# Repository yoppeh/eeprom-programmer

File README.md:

# eeprom-programmer
An Arduino Nano sketch and schematic for an Atmel 28cx programmer. The schematic started out only targeting 8kx8 chips (rev. A) but has been updated to connect all address lines for the 28cx series (rev. B), so any of those eeproms should work up to the 32kx8 chips. The design is based on [this one](https://youtu.be/K88pgWhEb1M), from Ben Eater. 

The Arduino Nano sketch implements a serial interface to the programmer. It accepts one-letter commands:
- e - erase the eeprom
- f - fill eeprom with incrementing bytes
- h - help (this) text
- l - lock the eeprom against writes
- r - read and dump eeprom contents
- s - set the size of the eeprom
- u - unlock eeprom writes
- v - software version info
- x - xmodem transfer binary file to eeprom

Any standard terminal program can be used to talk to the programmer. I use the following:
- [serial](http://www.decisivetactics.com/products/serial/) for the Mac
- [teraterm](https://ttssh2.osdn.jp/index.html.en) for Windows
- [minicom](https://linux.die.net/man/1/minicom) for Linux

Be sure to set the size of your target eeprom with the s command before doing anything. It doesn't affect the chip in any way, but tells the programmer what size your chip is for the erase, fill and read commands and error checking in the xmodem transfer.

The programmer uses standard x-modem, as provided by any respectable terminal program—and certainly all of the
above listed terminal programs—to put binary files onto the eeprom. No other software is required. The programmer
will verify every 64 bytes as they are written (the size of an internal eeprom page).

Although the eeprom chips are supposed to come from the factory unlocked, I've heard stories of some chips being
purchased off ebay that arrive locked. Try doing an unlock on a chip if you have problems writing to it.

When doing an xmodem transfer to the chip, the program will wait indefinitely for you to start the xmodem transfer from your terminal software. You can abort the transfer at this point by pressing the ESC key. Otherwise, once you have started the transfer, it will continue until the process completes or an error is detected.

If you want to fill the eeprom with a specific byte, say the 6502 nop 0xea, just change

    fill[j] = i + j; 
on line 490 to

    fill[j] = 0xea;

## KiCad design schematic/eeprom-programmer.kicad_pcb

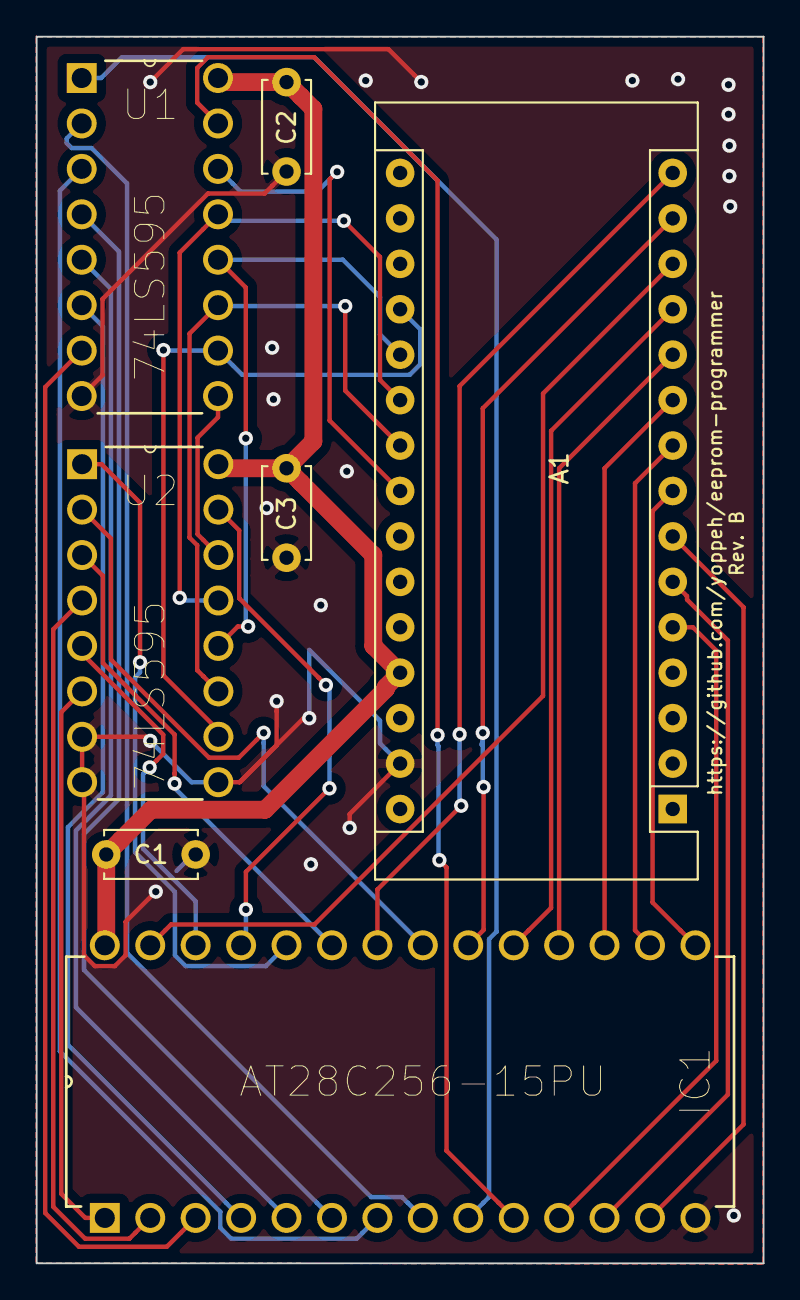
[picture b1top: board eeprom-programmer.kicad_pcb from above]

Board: 2 copper layers, 40.6 x 68.6 mm, 7 parts (0 on the bottom side), 34 nets.

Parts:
A1: Arduino_Nano_v3.x; Arduino_Nano
C1, C2, C3: .1uf; C_Disc_D5.0mm_W2.5mm_P5.00mm
IC1: AT28C256-15PU; DIP254P1524X482-28
U1, U2: 74LS595; DIP254P762X508-16

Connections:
/addr00: IC1.10, U1.15
/addr01: IC1.9, U1.1
/addr02: IC1.8, U1.2
/addr03: IC1.7, U1.3
/addr04: IC1.6, U1.4
/addr05: IC1.5, U1.5
/addr06: IC1.4, U1.6
/addr07: IC1.3, U1.7
/addr08: IC1.25, U2.15
/addr09: IC1.24, U2.1
/addr10: IC1.21, U2.2
/addr11: IC1.23, U2.3
/addr12: IC1.2, U2.4
/addr13: IC1.26, U2.5
/addr14: IC1.1, U2.6
/data0: A1.5, IC1.11
/data1: A1.6, IC1.12
/data2: A1.7, IC1.13
/data3: A1.8, IC1.15
/data4: A1.9, IC1.16
/data5: A1.10, IC1.17
/data6: A1.11, IC1.18
/data7: A1.12, IC1.19
Arduino5V: A1.27, C1.2, C2.2, C3.2, IC1.28, U1.16, U2.16
GND: A1.29, C1.1, C2.1, C3.1, IC1.14, U1.8, U2.7, U2.8, U2.9
unnamed: U1.9, U2.14
eeNotChipEnable: A1.14, IC1.20
eeNotOutputEnable: A1.15, IC1.22
eeNotWriteEnable: A1.13, IC1.27
srNotOutputEnable: A1.21, U1.13, U2.13
srNotResetAll: A1.19, U1.10, U2.10
srReadClock: A1.20, U1.12, U2.12
srSerialClock: A1.22, U1.11, U2.11
srSerialData: A1.23, U1.14

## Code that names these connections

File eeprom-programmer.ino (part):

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 *     PORTD, bit 3 = I/O1
 *     PORTD, bit 2 = I/O0
 */
const int srSerialData = A4;
const int srSerialClock = A3;
const int srNotOutputEnable = A2;
const int srReadClock = A1;
const int srNotResetAll = A0;
const int eeNotWriteEnable = 10;
const int eeNotChipEnable = 11;
const int eeNotOutputEnable = 12;
const int eeD0 = 2;
const int eeD1 = 3;
const int eeD2 = 4;
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 */
void setup() 
{
    pinMode(srSerialData, OUTPUT);
    pinMode(srSerialClock, OUTPUT);
    pinMode(srNotOutputEnable, OUTPUT);
    pinMode(srReadClock, OUTPUT);
    pinMode(srNotResetAll, OUTPUT);
    pinMode(eeNotWriteEnable, OUTPUT);
    pinMode(eeNotChipEnable, OUTPUT);
    pinMode(eeNotOutputEnable, OUTPUT);
  
    pinMode(LED_BUILTIN, OUTPUT);
    
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
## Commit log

2019-04-11 Tidy up the schematic a bit
2019-04-17 Rearrange the repo
2019-04-17 Add local library
2019-04-17 Rename files
2019-04-17 Readd Arduino and EEPROM symbols
2019-04-17 Remove excess wires
2019-04-17 Add busses
2019-04-17 Tighten up schematic
2019-04-18 Add PCB
2019-04-19 Initial PCB routing
2019-04-19 Fix issues for OSHPARK submission
2019-04-20 First prototype board
2019-04-21 Add verify to xmodem write
2019-04-23 Add evidence of existence
2019-04-23 Sync comments with code changes
2019-04-23 Auto-display help output on startup
2019-04-23 Add more text to README
2019-04-23 Fix whitespace
2019-04-24 Add picture of terminal window
2019-04-26 Use assets branch
2019-04-26 Fix image syntax for serial screenshot
2019-04-26 Show the screenshot without the text
2019-04-26 Remove images
2019-05-04 Port mappings changed for PCB
2019-05-04 Change revision to 'a'
2019-05-06 Update for schematic changes
2019-05-06 Remove pointless shift
2019-05-07 Remove executable permissions
2019-05-07 Use better design thresholds
2019-05-07 Begin new layout using better design limits
2019-05-07 Rearrange parts
2019-05-07 Add routing
2019-05-08 Add edge cuts
2019-05-08 Add ground fills and silkscreen
2019-05-08 Update solder mask clearance for Osh Park specs
2019-05-08 Right justify silkscreen ID text
2019-05-09 Fix permissions
2019-05-24 Add image of populated board
2019-05-24 Add version info to commands
2019-05-24 update readme for new s command
2019-12-06 Updated schematic to handle up to 32Kx8 eeproms with no rewiring
2019-12-07 Fixed timeout too fast waiting for user to start xmodem transfer
2019-12-07 Updated readme and gitignore
2019-12-07 Allow changing eeprom size at runtime
2019-12-07 Fix xmodem protocol
2019-12-07 Update README for code changes
2019-12-07 Update README to warn current PCB layout only supports 8kx8 roms
2019-12-08 Add chip name to size
2019-12-08 Formatting fix
2020-01-04 Update PCB layout to handle up to 64kx8 eeproms
2020-03-28 Update PCB layout to handle up to 32kx8 eeproms
2020-10-11 Fix assigment instead of comparison
